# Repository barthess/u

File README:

A ChibiOS based autopilot. 

Goals of project:

0. Fun.
1. Education.

Copyright (C) 2012 Uladzimir Pylinski aka barthess (barthess@yandex.ru)

This program is free software: you can redistribute it and/or modify
it under the terms of the GNU General Public License as published by
the Free Software Foundation, either version 3 of the License, or
(at your option) any later version.

This program is distributed in the hope that it will be useful,
but WITHOUT ANY WARRANTY; without even the implied warranty of
MERCHANTABILITY or FITNESS FOR A PARTICULAR PURPOSE.  See the
GNU General Public License for more details.

You should have received a copy of the GNU General Public License
along with this program.  If not, see <http://www.gnu.org/licenses/>.

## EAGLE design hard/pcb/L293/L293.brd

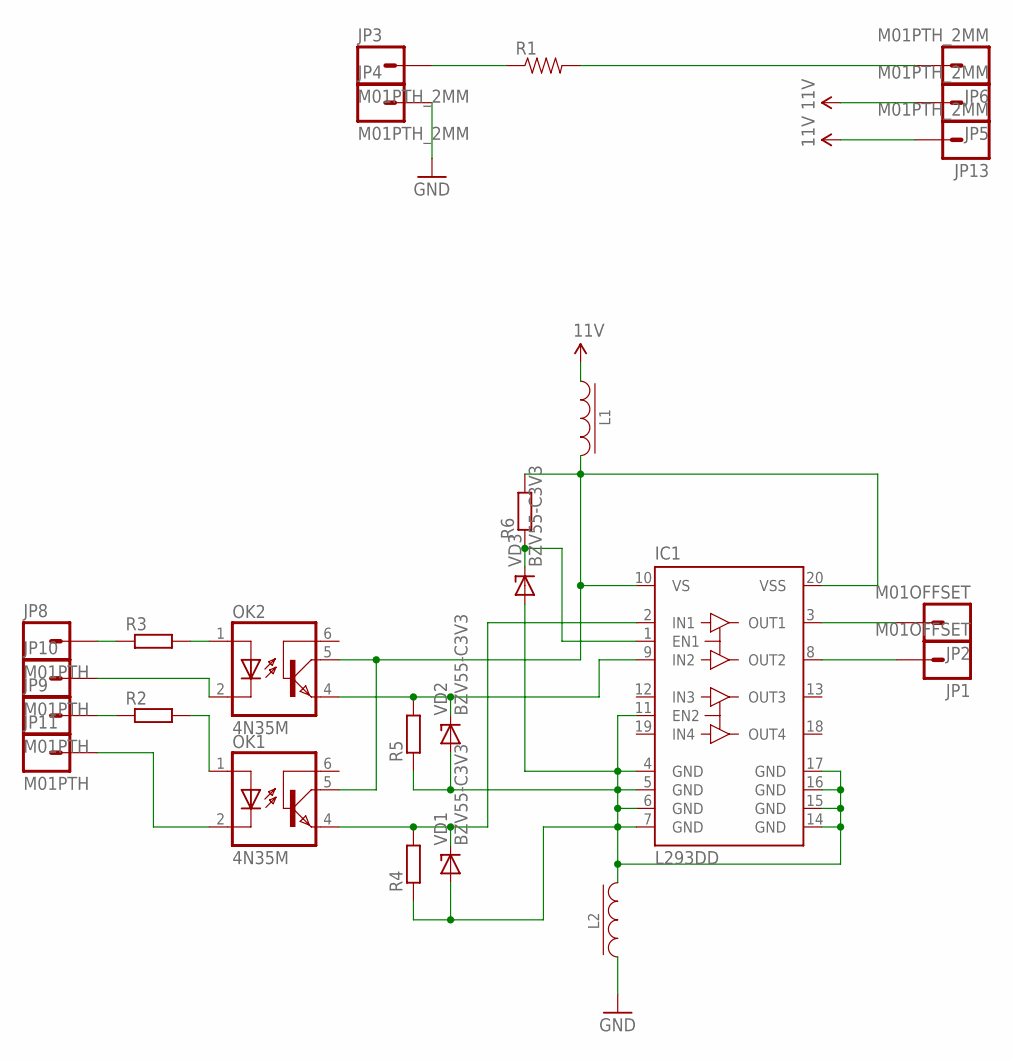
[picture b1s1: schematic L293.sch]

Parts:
IC1: L293DD; SO20
JP1, JP2: M01OFFSET; 1X01_OFFSET
JP3, JP4, JP5, JP6, JP13: M01PTH_2MM; 1X01_2MM
JP8, JP9, JP10, JP11: M01PTH; 1X01
L1, L2: DRA127
OK1, OK2: 4N35M; DIL06
R1: RESISTOR2512; R2512
R2, R3, R4, R5, R6: RESISTOR0805; 0805
VD1, VD2, VD3: BZV55-C3V3; SOD80C

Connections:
1.0V: JP5.1, JP13.1, L1.1
GND: JP4.1, L2.1
GND_DIRT: IC1.4 (GND), IC1.5 (GND), IC1.6 (GND), IC1.7 (GND), IC1.11 (EN2), IC1.14 (GND), IC1.15 (GND), IC1.16 (GND), IC1.17 (GND), L2.2, R4.1, R5.1, VD1.A, VD2.A, VD3.A
unnamed: IC1.8 (OUT2), JP1.1
unnamed: IC1.3 (OUT1), JP2.1
unnamed: JP3.1, R1.1
unnamed: JP6.1, R1.2
unnamed: JP9.1, R2.1
unnamed: JP8.1, R3.1
unnamed: IC1.10 (VS), IC1.20 (VSS), L1.2, OK1.5 (COL), OK2.5 (COL), R6.2
unnamed: OK1.1 (A), R2.2
unnamed: JP11.1, OK1.2 (C)
unnamed: JP10.1, OK2.2 (C)
unnamed: OK2.1 (A), R3.2
unnamed: IC1.1 (EN1), R6.1, VD3.C
unnamed: IC1.9 (IN2), OK2.4 (EMI), R5.2, VD2.C
unnamed: IC1.2 (IN1), OK1.4 (EMI), R4.2, VD1.C

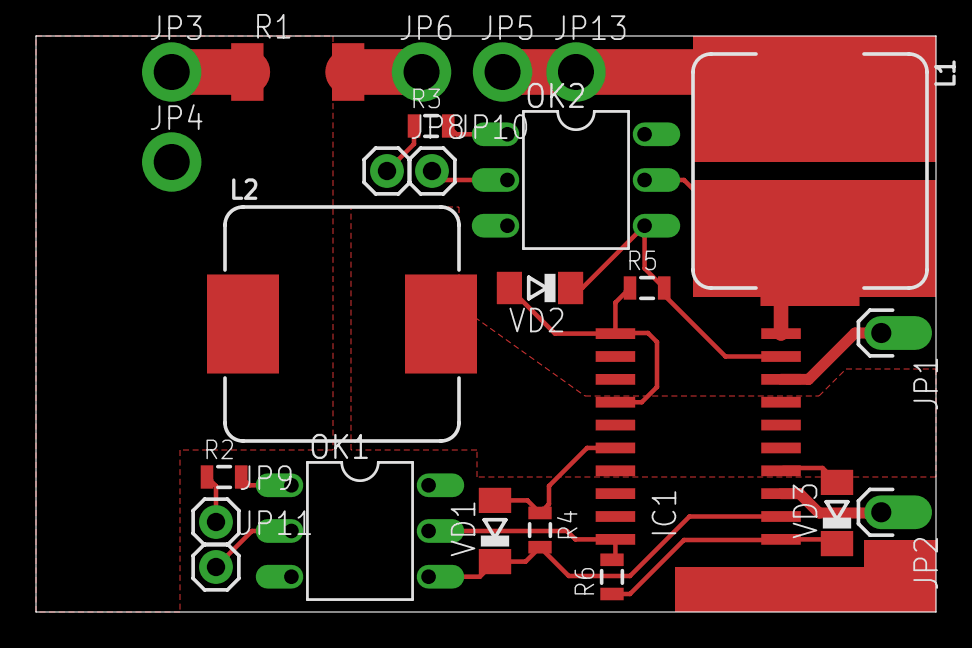
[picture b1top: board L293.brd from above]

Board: 2 copper layers, 50.0 x 32.0 mm, 25 parts (0 on the bottom side), 17 nets.

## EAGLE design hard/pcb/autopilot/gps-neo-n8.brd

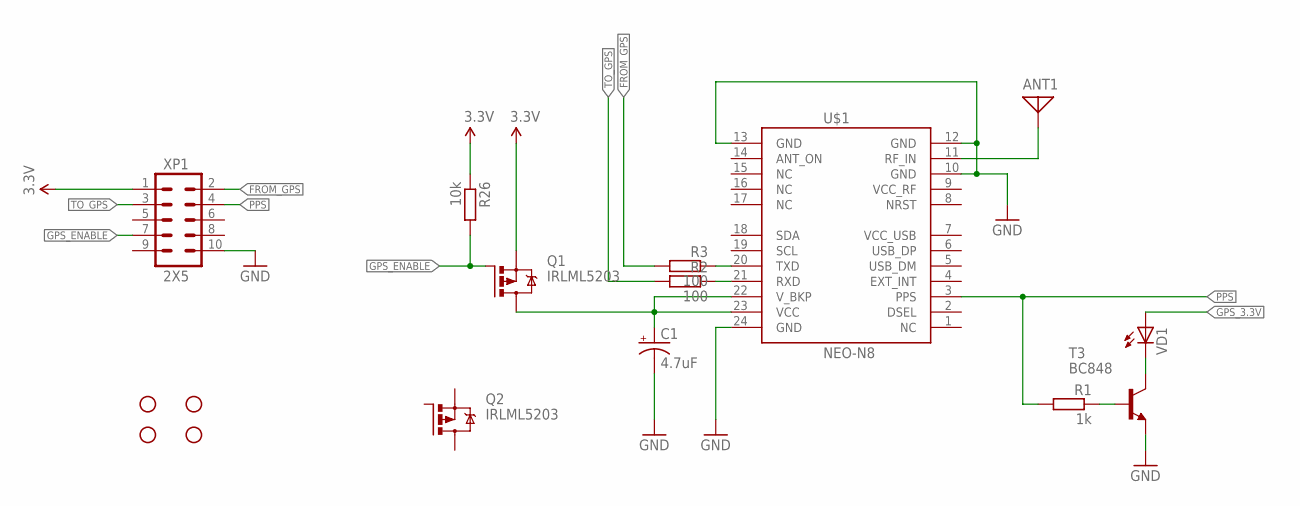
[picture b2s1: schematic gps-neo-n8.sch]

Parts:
ANT1: GPS_ANTENNA'35X35'; GPS_ANT_35X35MM
C1: 4.7uF; EIA3216-KIT
JP1, JP2, JP4, JP5: STAND-OFF
Q1, Q2: IRLML5203; MICRO3
R1: 1k; R0805
R2, R3: 100; R0805
R26: 10k; R0805
T3: BC848; SOT23
U$1: NEO-N8; NEO-M8
VD1: LED0805; LED-0805
XP1: 2X5; 2X5-PSEUDOSMD

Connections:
3.3V: Q1.2 (S), R26.1, XP1.1
FROM_GPS: R3.2, XP1.2
GND: C1.C (-), T3.2 (E), U$1.10 (GND), U$1.12 (GND), U$1.13 (GND), U$1.24 (GND), XP1.10
GPS_3.3V: C1.A (+), Q1.3 (D), U$1.22 (V_BKP), U$1.23 (VCC), VD1.A
GPS_ENABLE: Q1.1 (G), R26.2, XP1.7
unnamed: T3.3 (C), VD1.C
unnamed: ANT1.1, U$1.11 (RF_IN)
unnamed: R1.1, T3.1 (B)
unnamed: R2.1, U$1.21 (RXD)
unnamed: R3.1, U$1.20 (TXD)
PPS: R1.2, U$1.3 (PPS), XP1.4
TO_GPS: R2.2, XP1.3
VCC_RF: U$1.9 (VCC_RF)

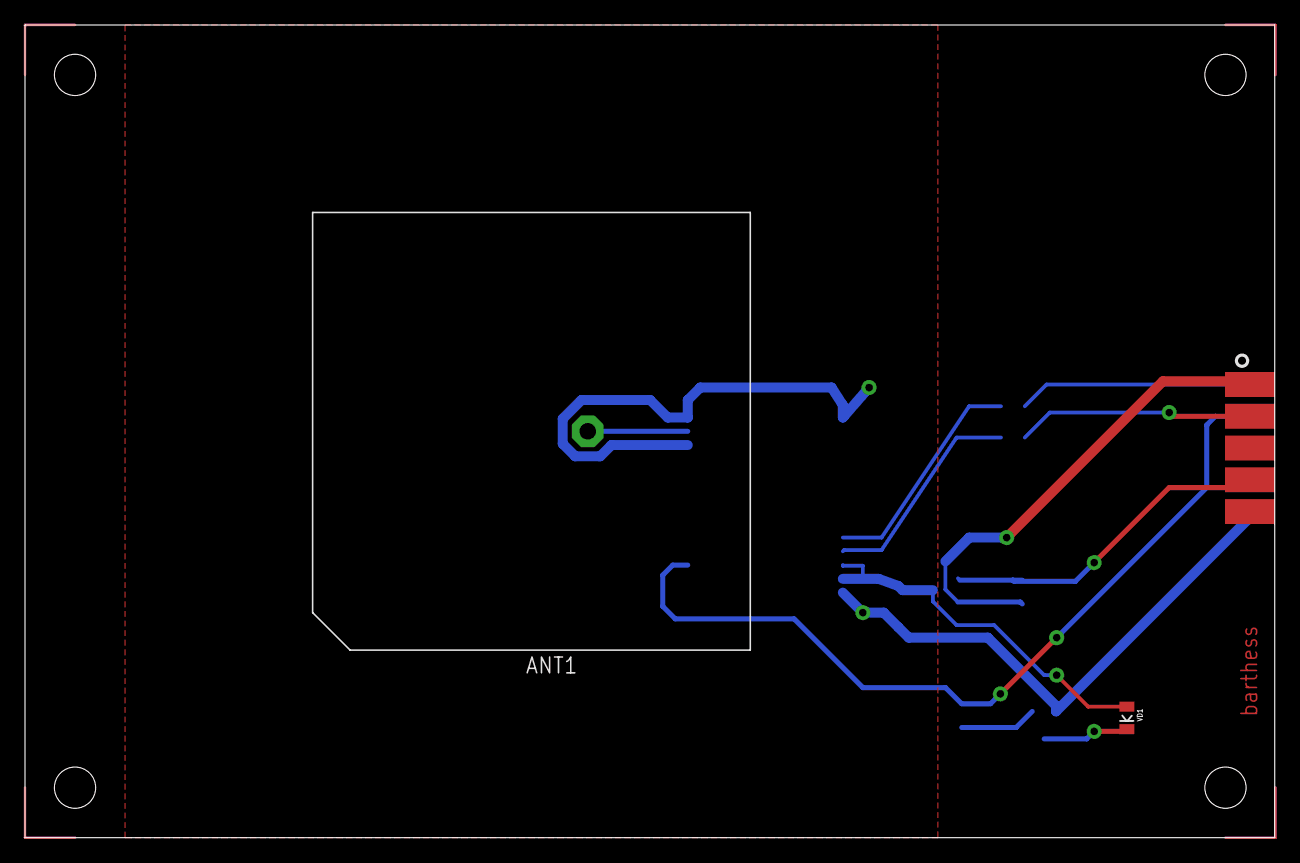
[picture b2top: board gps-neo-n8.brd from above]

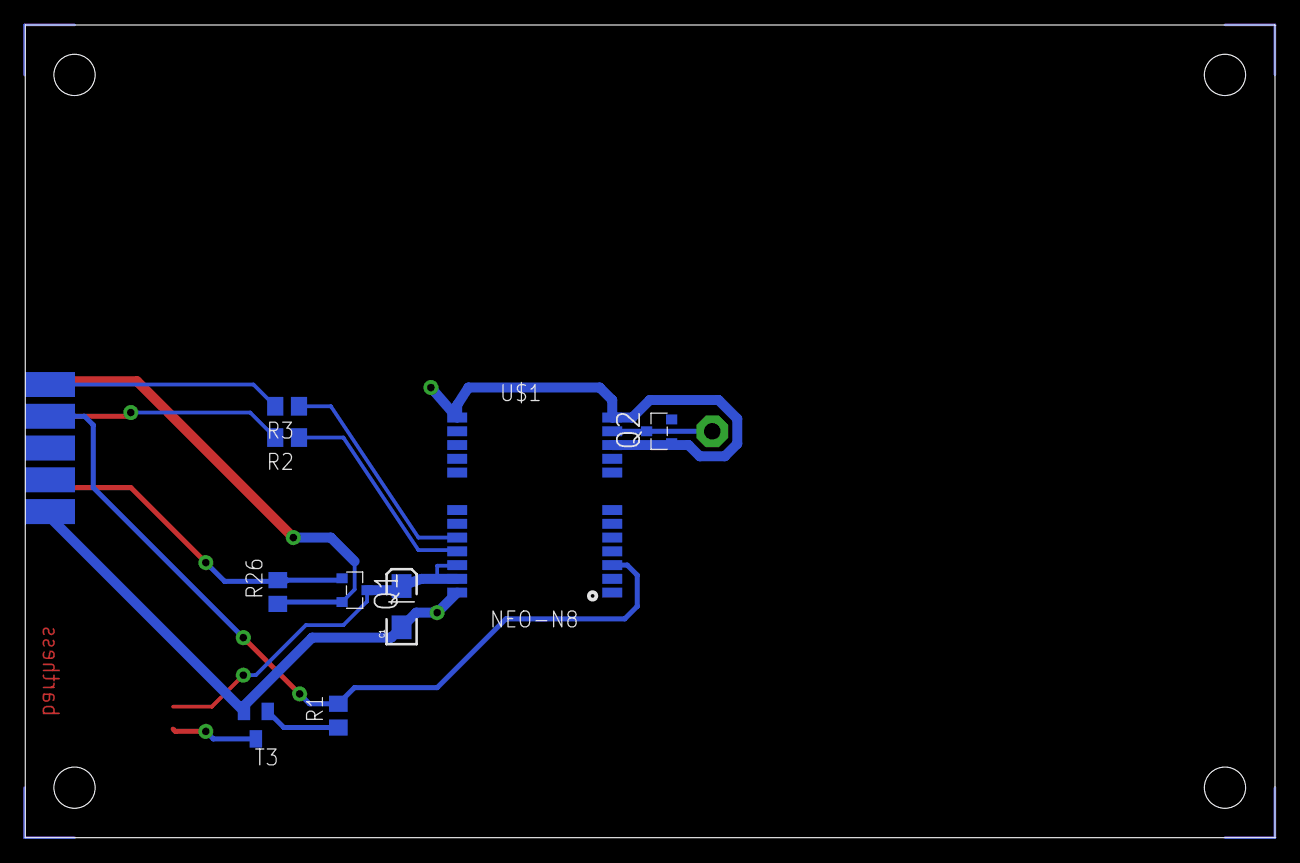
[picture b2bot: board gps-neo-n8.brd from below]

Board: 2 copper layers, 99.9 x 65.0 mm, 17 parts (9 on the bottom side), 12 nets.

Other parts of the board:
U$2: LOGO_CHIBIOS_SIGNAL

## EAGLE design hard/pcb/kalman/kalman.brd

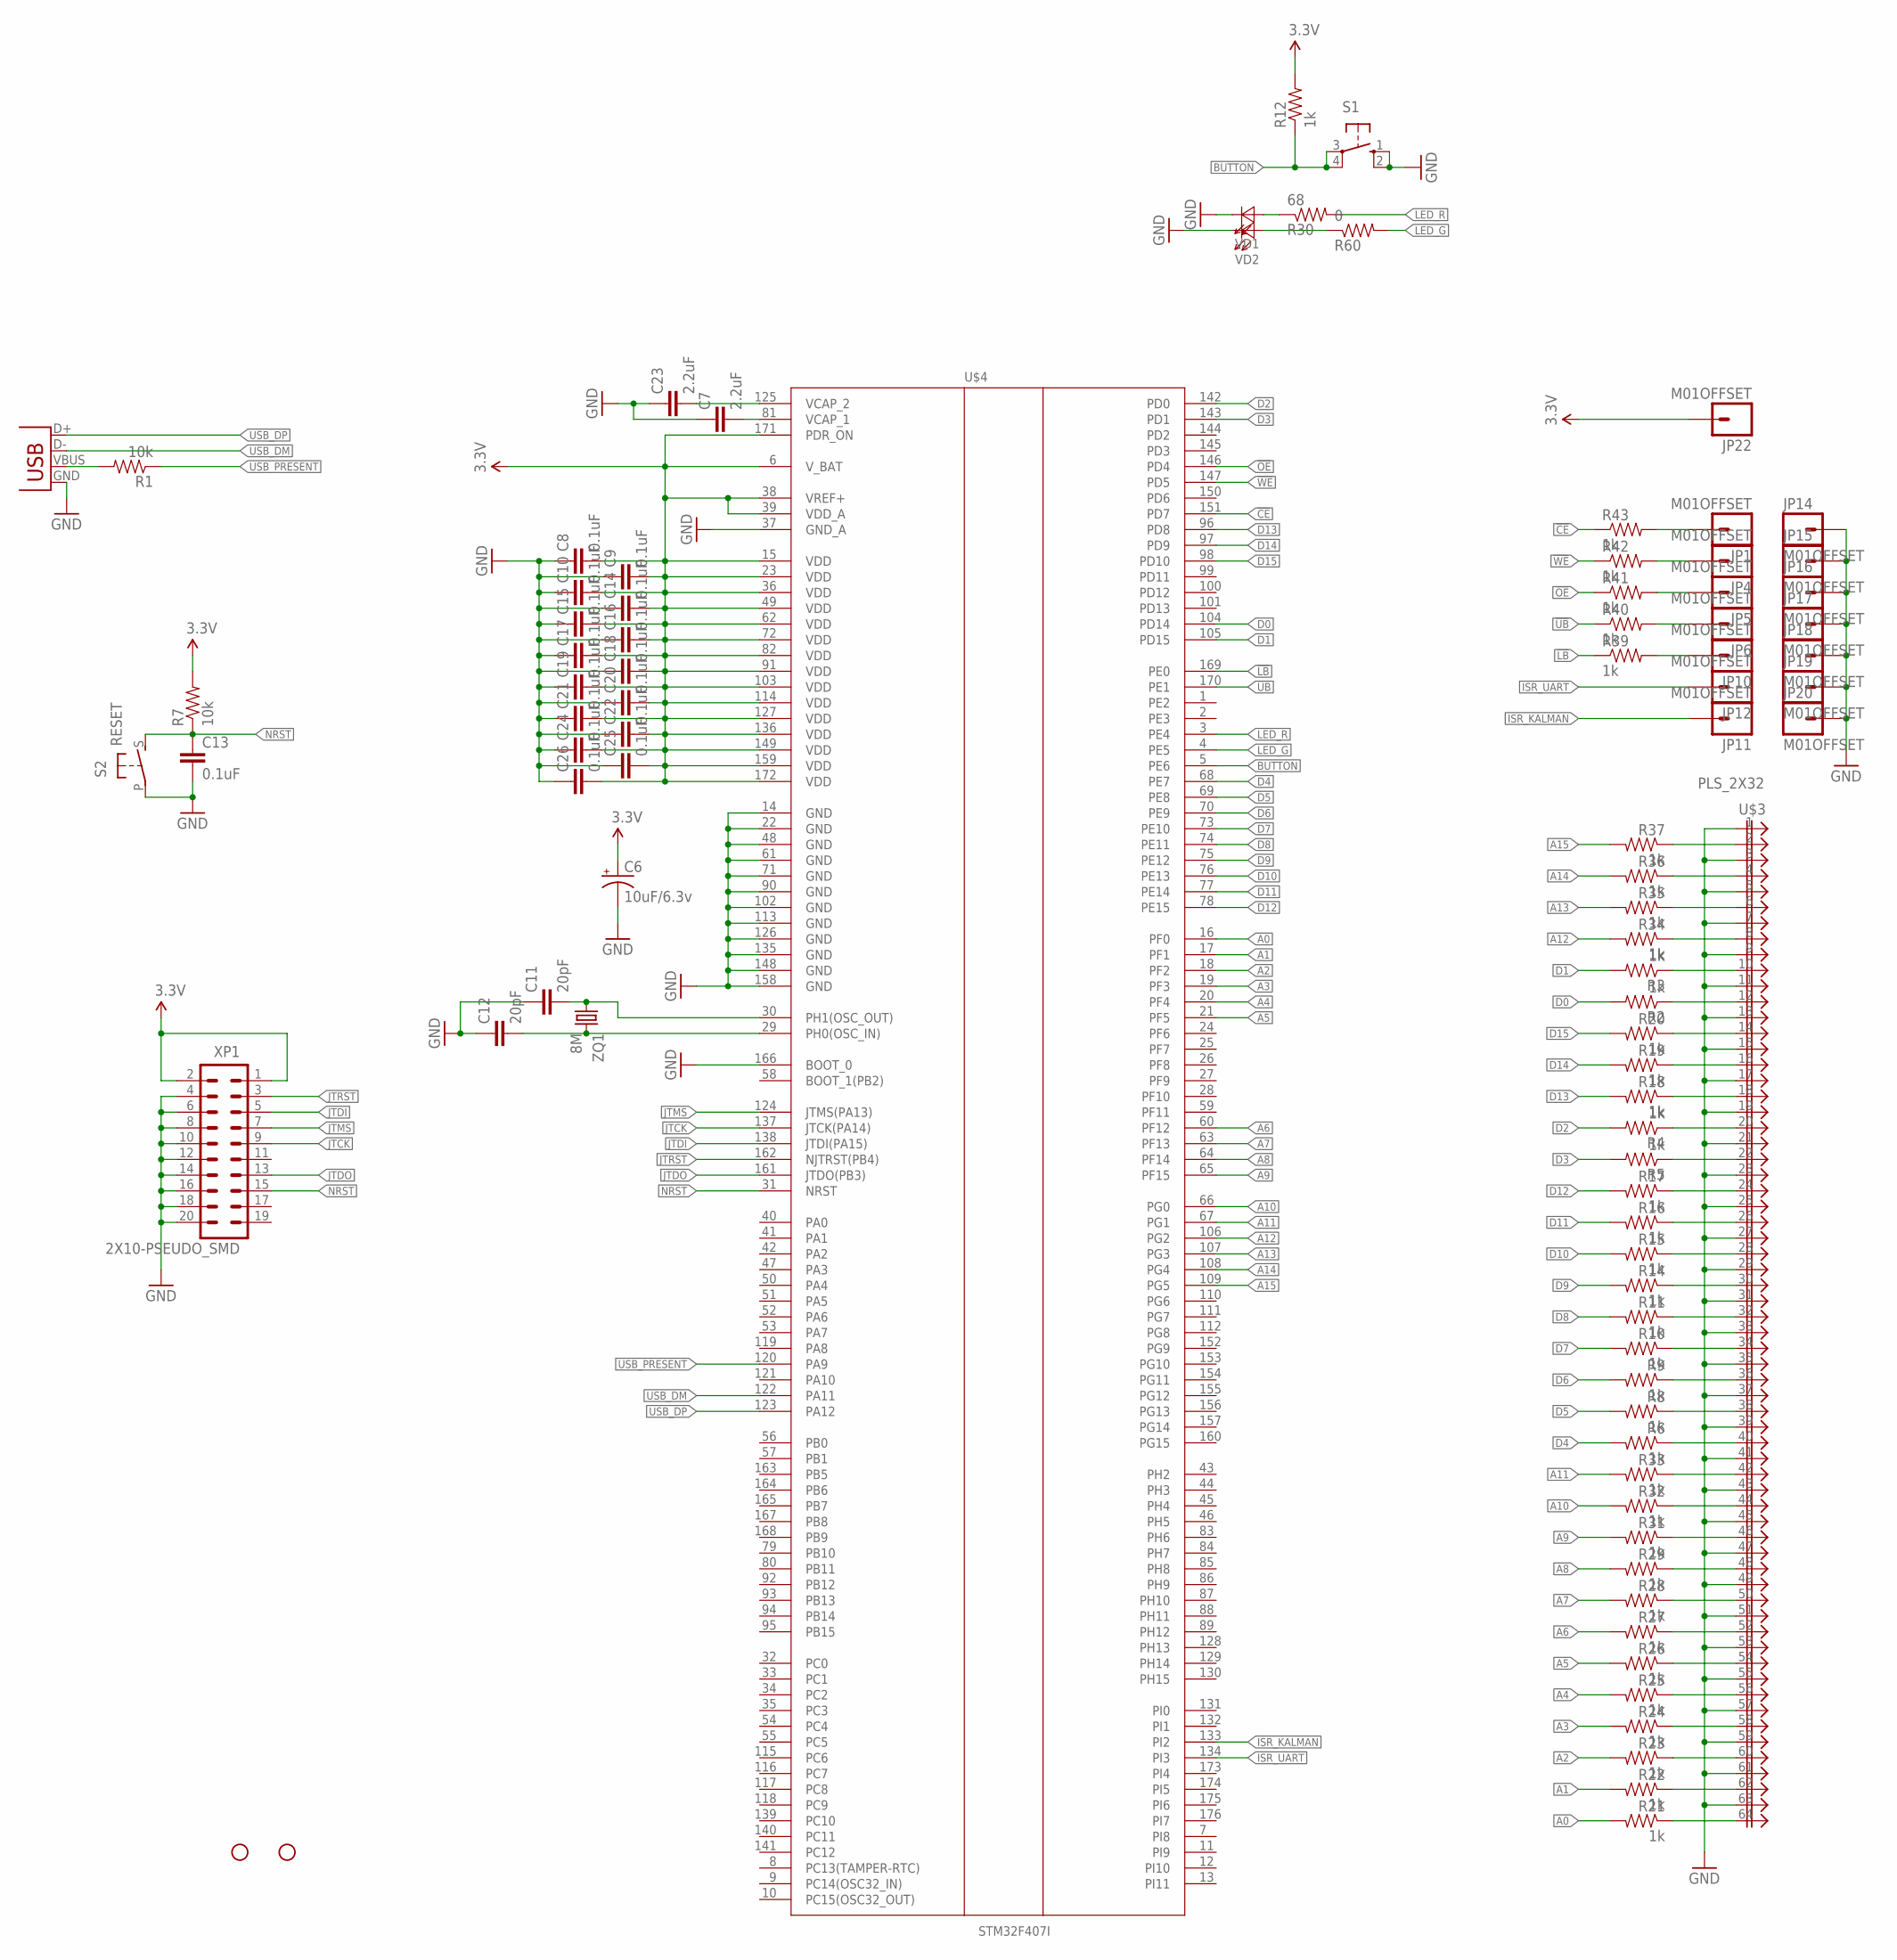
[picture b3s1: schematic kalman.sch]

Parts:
C6: 10uF/6.3v; EIA3216-KIT
C7, C23: 2.2uF; 0805
C8, C9, C10, C13, C14, C15, C16, C17, C18, C19, C20, C21, C22, C24, C25, C26: 0.1uF; 0805
C11, C12: 20pF; 0805
JP1, JP4, JP5, JP6, JP10, JP11, JP12, JP14, JP15, JP16, JP17, JP18, JP19, JP20, JP22: M01OFFSET; 1X01_OFFSET
JP7, JP8: STAND-OFF
R1, R7: 10k; 0805
R2, R3, R4, R5, R6, R8, R9, R10, R11, R12, R14, R15, R16, R17, R18, R19, R20, R21, R22, R23, R24, R25, R26, R27, R28, R29, R31, R32, R33, R34, R35, R36, R37, R39, R40, R41, R42, R43: 1k; 0805
R30: 68; 0805
R60: 0; 0805
S1: 10-XX; B3F-10XX
S2: RESET; BUTTON_6X3.5
U$3: PLS_2X32; PLS_2X32_PSEUDOSMD
U$4: STM32F407I; TQFP176(1.5X0.25)
VD1, VD2: LED1206; LED-1206
X1: USB-SMD-NS; USB-MINIB-NOSTOP
XP1: 2X10-PSEUDO_SMD; PLD_2X10_PSEUDOSMD
ZQ1: 8M; CTS406

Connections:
3.3V: C6.A (+), C8.2, C9.2, C10.2, C14.2, C15.2, C16.2, C17.2, C18.2, C19.2, C20.2, C21.2, C22.2, C24.2, C25.2, C26.2, JP22.1, R7.2, R12.2, U$4.6 (V_BAT), U$4.15 (VDD), U$4.23 (VDD), U$4.36 (VDD), U$4.38 (VREF+), U$4.39 (VDD_A), U$4.49 (VDD), U$4.62 (VDD), U$4.72 (VDD), U$4.82 (VDD), U$4.91 (VDD), U$4.103 (VDD), U$4.114 (VDD), U$4.127 (VDD), U$4.136 (VDD), U$4.149 (VDD), U$4.159 (VDD), U$4.171 (PDR_ON), U$4.172 (VDD), XP1.1, XP1.2
5V_USB: R1.2, X1.VBUS
!CE: R43.1, U$4.151 (PD7)
!LB: R39.1, U$4.169 (PE0)
!OE: R41.1, U$4.146 (PD4)
!UB: R40.1, U$4.170 (PE1)
!WE: R42.1, U$4.147 (PD5)
A0: R21.2, U$4.16 (PF0)
A1: R22.2, U$4.17 (PF1)
A2: R23.2, U$4.18 (PF2)
A3: R24.2, U$4.19 (PF3)
A4: R25.2, U$4.20 (PF4)
A5: R26.2, U$4.21 (PF5)
A6: R27.2, U$4.60 (PF12)
A7: R28.2, U$4.63 (PF13)
A8: R29.2, U$4.64 (PF14)
A9: R31.2, U$4.65 (PF15)
A10: R32.2, U$4.66 (PG0)
A11: R33.2, U$4.67 (PG1)
A12: R34.2, U$4.106 (PG2)
A13: R35.2, U$4.107 (PG3)
A14: R36.2, U$4.108 (PG4)
A15: R37.2, U$4.109 (PG5)
BUTTON: R12.1, S1.3, S1.4 (P1), U$4.5 (PE6)
D0: R2.2, U$4.104 (PD14)
D1: R3.2, U$4.105 (PD15)
D2: R4.2, U$4.142 (PD0)
D3: R5.2, U$4.143 (PD1)
D4: R6.2, U$4.68 (PE7)
D5: R8.2, U$4.69 (PE8)
D6: R9.2, U$4.70 (PE9)
D7: R10.2, U$4.73 (PE10)
D8: R11.2, U$4.74 (PE11)
D9: R14.2, U$4.75 (PE12)
D10: R15.2, U$4.76 (PE13)
D11: R16.2, U$4.77 (PE14)
D12: R17.2, U$4.78 (PE15)
D13: R18.2, U$4.96 (PD8)
D14: R19.2, U$4.97 (PD9)
D15: R20.2, U$4.98 (PD10)
GND: C6.C (-), C7.1, C8.1, C9.1, C10.1, C11.1, C12.1, C13.2, C14.1, C15.1, C16.1, C17.1, C18.1, C19.1, C20.1, C21.1, C22.1, C23.1, C24.1, C25.1, C26.1, JP14.1, JP15.1, JP16.1, JP17.1, JP18.1, JP19.1, JP20.1, S1.1 (S), S1.2 (S1), S2.P, U$3.1, U$3.3, U$3.5, U$3.7, U$3.9, U$3.11, U$3.13, U$3.15, U$3.17, U$3.19, U$3.21, U$3.23, U$3.25, U$3.27, U$3.29, U$3.31, U$3.33, U$3.35, U$3.37, U$3.39, U$3.41, U$3.43, U$3.45, U$3.47, U$3.49, U$3.51, U$3.53, U$3.55, U$3.57, U$3.59, U$3.61, U$3.63, U$4.14 (GND), U$4.22 (GND), U$4.37 (GND_A), U$4.48 (GND), U$4.61 (GND), U$4.71 (GND), U$4.90 (GND), U$4.102 (GND), U$4.113 (GND), U$4.126 (GND), U$4.135 (GND), U$4.148 (GND), U$4.158 (GND), U$4.166 (BOOT_0), VD1.C, VD2.C, X1.GND, XP1.4, XP1.6, XP1.8, XP1.10, XP1.12, XP1.14, XP1.16, XP1.18, XP1.20
ISR_KALMAN: JP11.1, U$4.133 (PI2)
ISR_UART: JP12.1, U$4.134 (PI3)
JTCK: U$4.137 (JTCK(PA14)), XP1.9
JTDI: U$4.138 (JTDI(PA15)), XP1.5
JTDO: U$4.161 (JTDO(PB3)), XP1.13
JTMS: U$4.124 (JTMS(PA13)), XP1.7
JTRST: U$4.162 (NJTRST(PB4)), XP1.3
LED_G: R60.2, U$4.4 (PE5)
LED_R: R30.2, U$4.3 (PE4)
unnamed: C23.2, U$4.125 (VCAP_2)
unnamed: C7.2, U$4.81 (VCAP_1)
unnamed: JP1.1, R43.2
unnamed: R5.1, U$3.22
unnamed: R4.1, U$3.20
unnamed: R18.1, U$3.18
unnamed: R19.1, U$3.16
unnamed: R6.1, U$3.40
unnamed: R8.1, U$3.38
unnamed: R21.1, U$3.64
unnamed: R9.1, U$3.36
unnamed: R30.1, VD1.A
unnamed: R22.1, U$3.62
unnamed: R10.1, U$3.34
unnamed: R11.1, U$3.32
unnamed: R14.1, U$3.30
unnamed: R15.1, U$3.28
unnamed: R16.1, U$3.26
unnamed: R17.1, U$3.24
unnamed: R20.1, U$3.14
unnamed: C12.2, U$4.29 (PH0(OSC_IN)), ZQ1.3 (2)
unnamed: C11.2, U$4.30 (PH1(OSC_OUT)), ZQ1.1
unnamed: R2.1, U$3.12
unnamed: R3.1, U$3.10
unnamed: R23.1, U$3.60
unnamed: R24.1, U$3.58
unnamed: R25.1, U$3.56
unnamed: R26.1, U$3.54
unnamed: R27.1, U$3.52
unnamed: R28.1, U$3.50
unnamed: R60.1, VD2.A
unnamed: R29.1, U$3.48
unnamed: R31.1, U$3.46
unnamed: R32.1, U$3.44
unnamed: R33.1, U$3.42
unnamed: R34.1, U$3.8
unnamed: R35.1, U$3.6
unnamed: R36.1, U$3.4
unnamed: R37.1, U$3.2
unnamed: JP4.1, R42.2
unnamed: JP5.1, R41.2
unnamed: JP6.1, R40.2
unnamed: JP10.1, R39.2
NRST: C13.1, R7.1, S2.S, U$4.31 (NRST), XP1.15
USB_DM: U$4.122 (PA11), X1.D-
USB_DP: U$4.123 (PA12), X1.D+
USB_PRESENT: R1.1, U$4.120 (PA9)

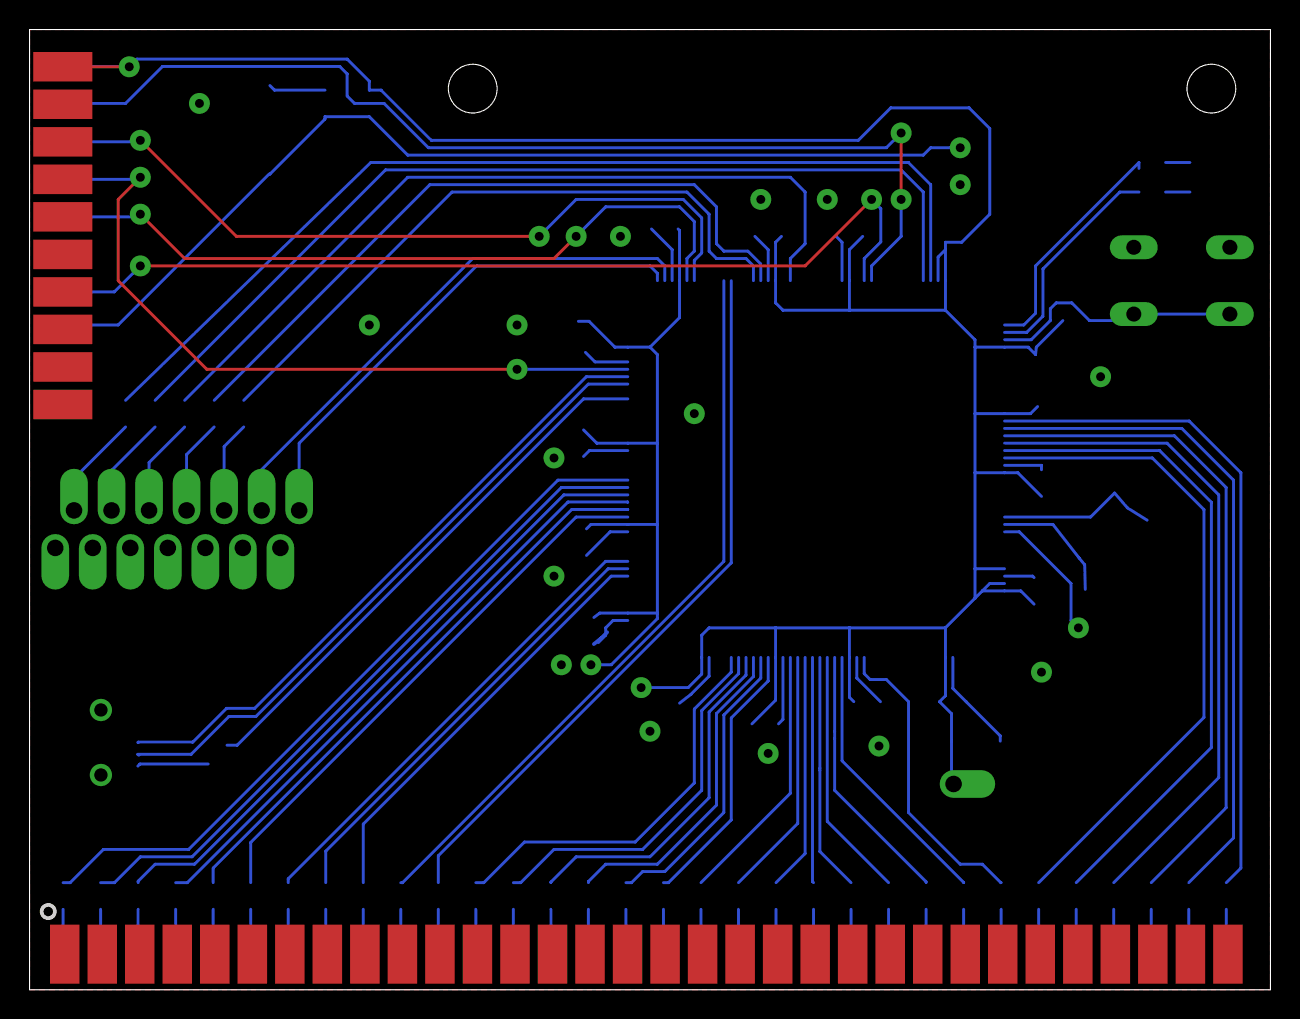
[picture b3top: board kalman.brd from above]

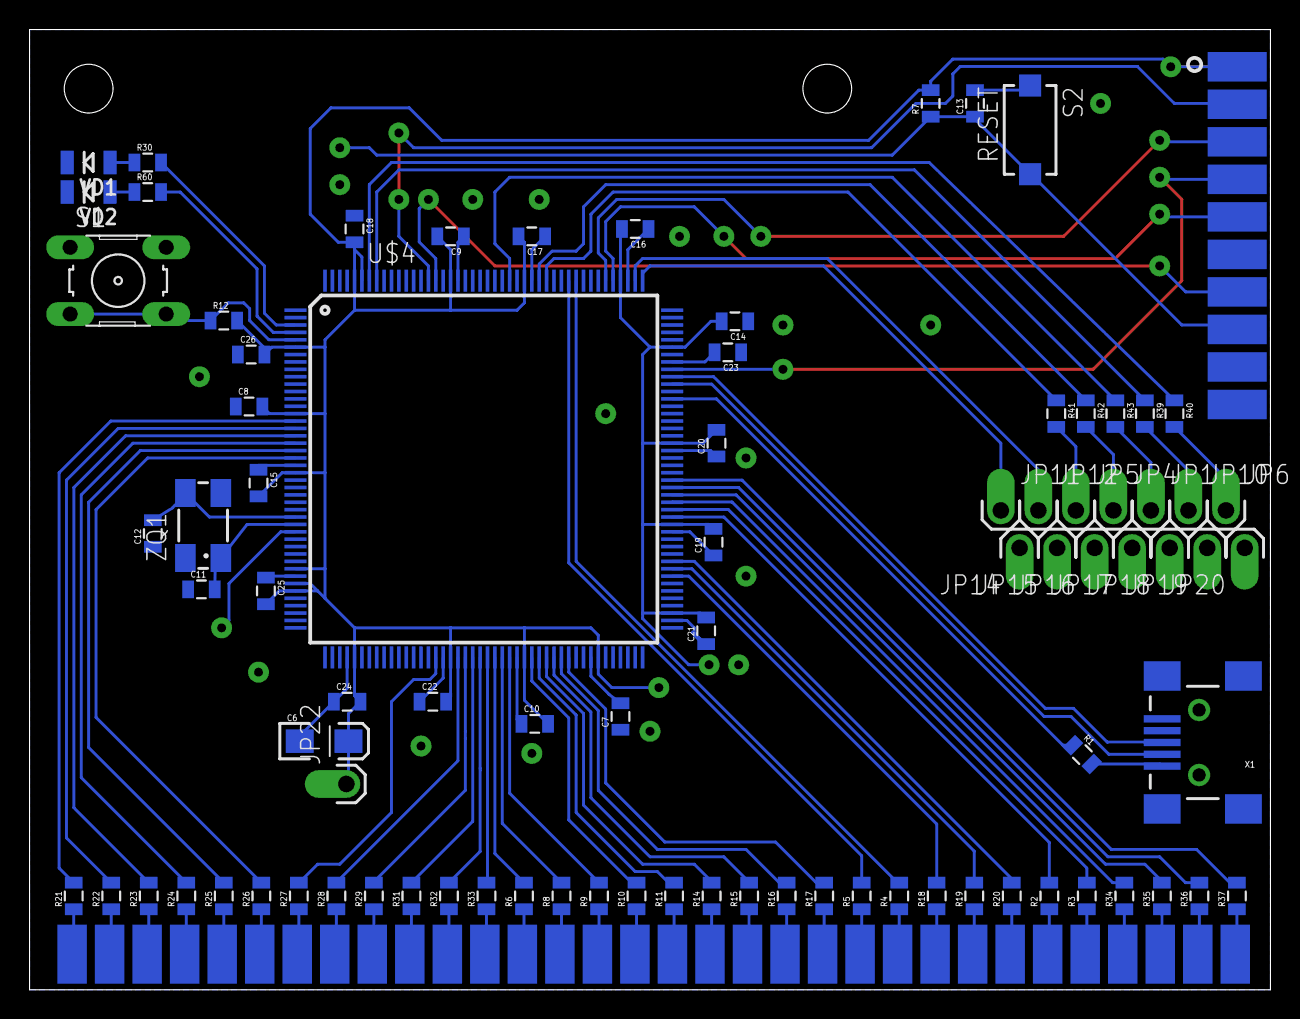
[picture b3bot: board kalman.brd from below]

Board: 2 copper layers, 84.0 x 65.0 mm, 89 parts (86 on the bottom side), 97 nets.

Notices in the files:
parts and their libraries:
SparkFun-Connectors: Licensing: Creative Commons ShareAlike 4.0 International - https://creativecommons.org/licenses/by-sa/4.0
SparkFun: Licensing: CC v3.0 Share-Alike You are welcome to use this library for commercial purposes.
inductor-cooper: Copyright (C) 2010, Bob Starr
